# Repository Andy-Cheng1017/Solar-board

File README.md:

# Solar-board
太陽能板12V轉5V

含測試程式

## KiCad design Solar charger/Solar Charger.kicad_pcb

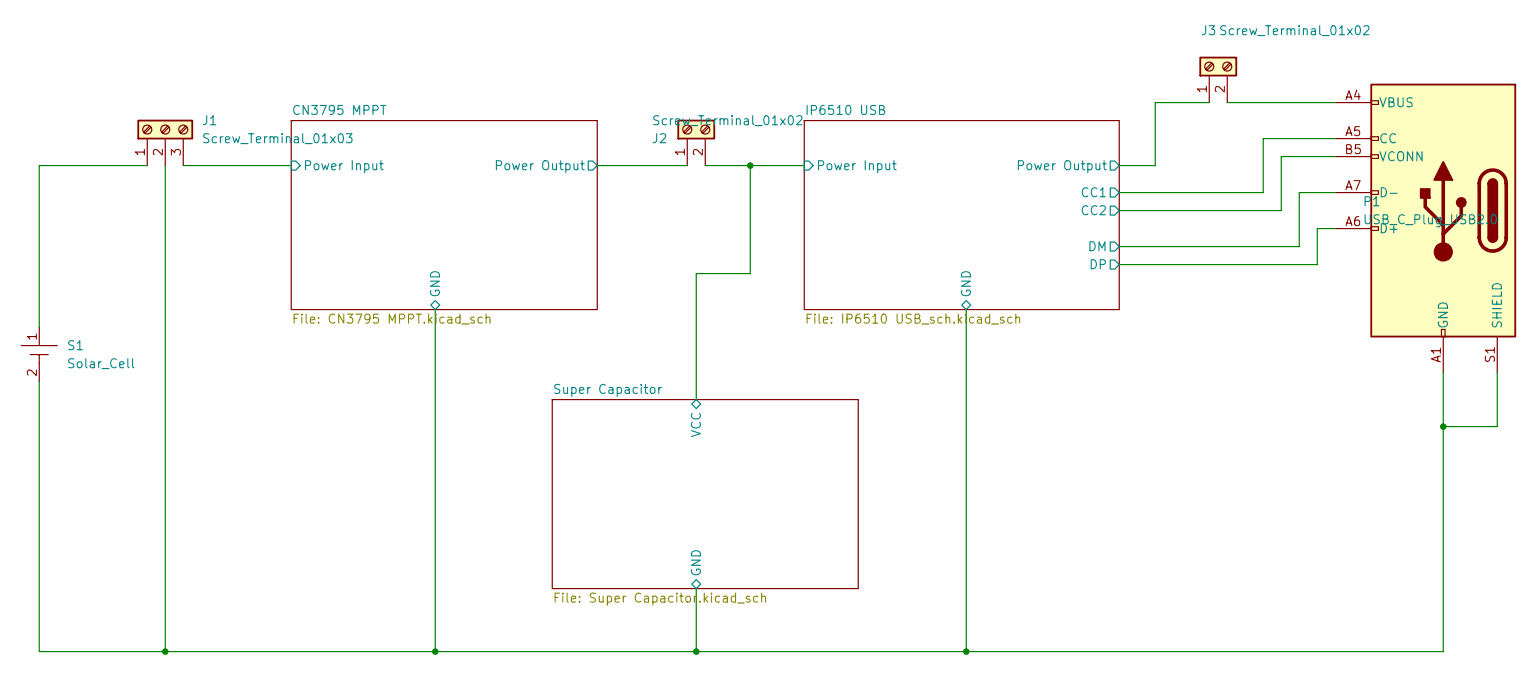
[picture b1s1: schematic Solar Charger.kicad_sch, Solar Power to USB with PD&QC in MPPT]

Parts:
J1: Screw_Terminal_01x03; TerminalBlock_bornier-3_P5.08mm
J2, J3: Screw_Terminal_01x02; TerminalBlock_bornier-2_P5.08mm
P1: USB_C_Plug_USB2.0; USB_C_Receptacle_HRO_TYPE-C-31-M-12
S1: Solar_Cell; TerminalBlock_bornier-2_P5.08mm

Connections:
/CN3795 MPPT/BAT: J2.1; also elsewhere on the board
/IP6510 USB/CC1: P1.A5 (CC); also elsewhere on the board
/IP6510 USB/CC2: P1.B5 (VCONN); also elsewhere on the board
/IP6510 USB/DM: P1.A7 (D-); also elsewhere on the board
/IP6510 USB/DP: P1.A6 (D+); also elsewhere on the board
/IP6510 USB/Power Input: J2.2; also elsewhere on the board
/IP6510 USB/Power Output: J3.1; also elsewhere on the board
GND: J1.2, P1.A1 (GND), P1.A12 (GND), P1.B1 (GND), P1.B12 (GND), P1.S1 (SHIELD), S1.2; also elsewhere on the board
unnamed: J1.1, S1.1
unnamed: J3.2, P1.A4 (VBUS), P1.A9 (VBUS), P1.B4 (VBUS), P1.B9 (VBUS)
VCC: J1.3; also elsewhere on the board

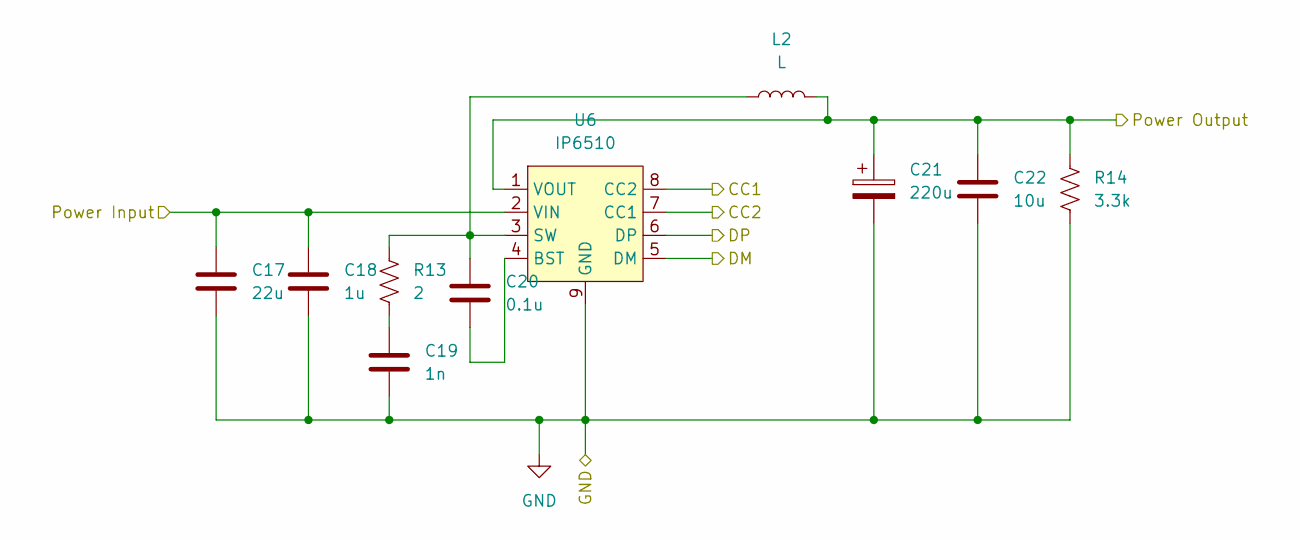
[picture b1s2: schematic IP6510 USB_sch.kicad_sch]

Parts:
C17: 22u; C_0805_2012Metric
C18: 1u; C_0805_2012Metric
C19: 1n; C_0805_2012Metric
C20: 0.1u; C_0805_2012Metric
C21: 220u; CP_Radial_D6.3mm_P2.50mm
C22: 10u; C_0805_2012Metric
L2: L; L_10.4x10.4_H4.8
R13: 2; R_0805_2012Metric
R14: 3.3k; R_0805_2012Metric
U6: IP6510; SOIC-8-1EP_3.9x4.9mm_P1.27mm_EP2.29x3mm_ThermalVias

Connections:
/IP6510 USB/CC1: U6.8 (CC2); also elsewhere on the board
/IP6510 USB/CC2: U6.7 (CC1); also elsewhere on the board
/IP6510 USB/DM: U6.5 (DM); also elsewhere on the board
/IP6510 USB/DP: U6.6 (DP); also elsewhere on the board
/IP6510 USB/Power Input: C17.1, C18.1, U6.2 (VIN); also elsewhere on the board
/IP6510 USB/Power Output: C21.1, C22.1, L2.2, R14.1, U6.1 (VOUT); also elsewhere on the board
GND: C17.2, C18.2, C19.2, C21.2, C22.2, R14.2, U6.9 (GND); also elsewhere on the board
unnamed: C19.1, R13.2
unnamed: C20.1, L2.1, R13.1, U6.3 (SW)
unnamed: C20.2, U6.4 (BST)

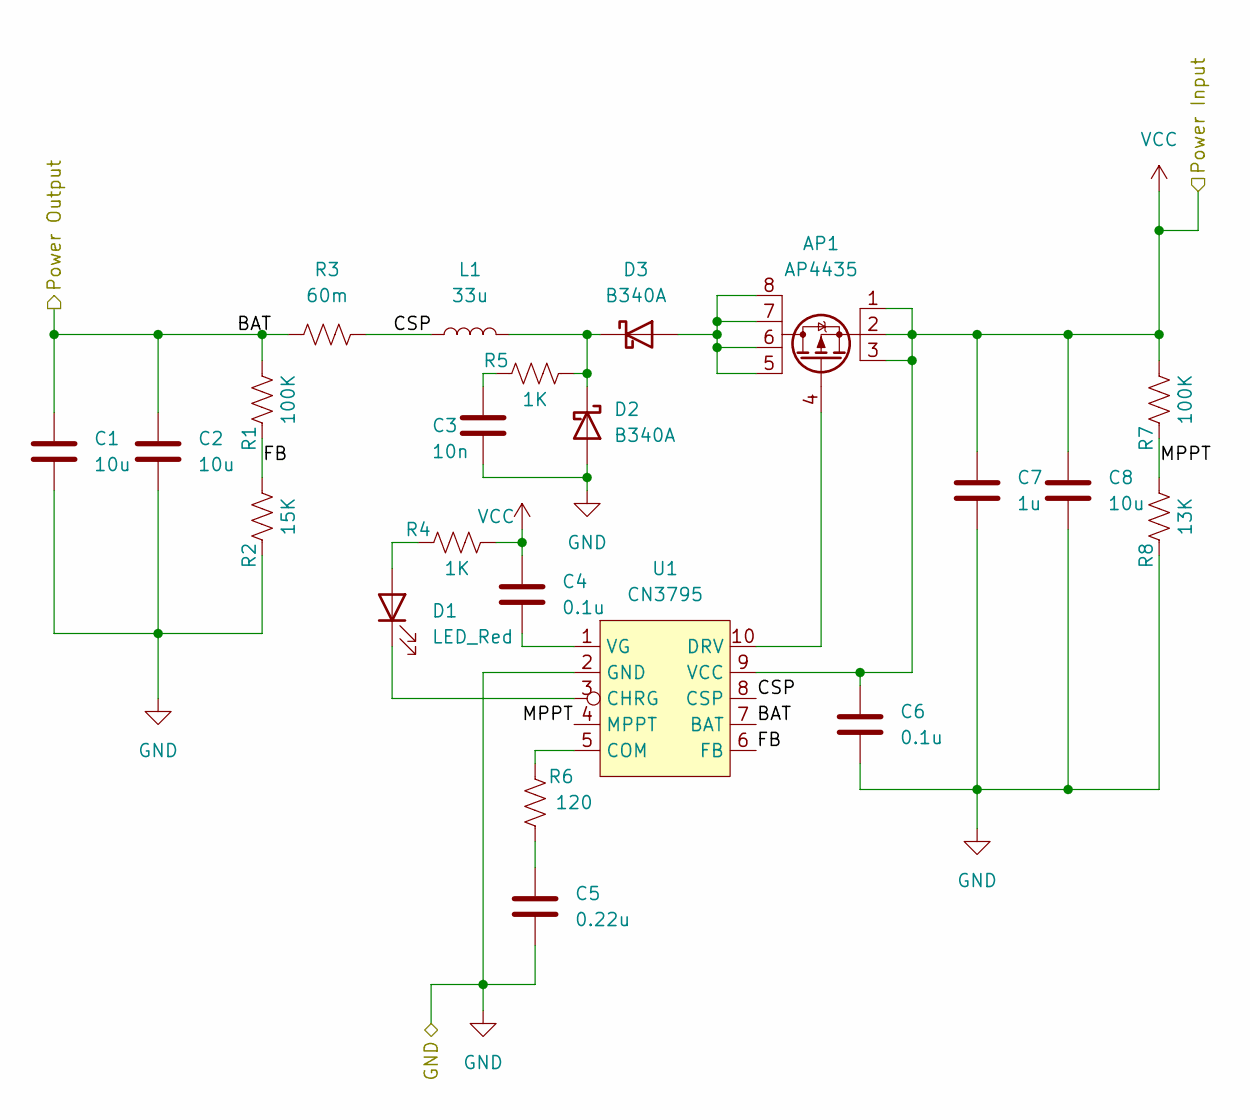
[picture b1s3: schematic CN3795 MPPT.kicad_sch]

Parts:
AP1: AP4435; PowerIntegrations_SO-8
C1, C2, C8: 10u; C_1206_3216Metric
C3: 10n; C_0805_2012Metric
C4, C6: 0.1u; C_0805_2012Metric
C5: 0.22u; C_0805_2012Metric
C7: 1u; C_0805_2012Metric
D1: LED_Red; LED_0805_2012Metric
D2, D3: B340A; D_SMA
L1: 33u; L_10.4x10.4_H4.8
R1, R7: 100K; R_0805_2012Metric
R2: 15K; R_0805_2012Metric
R3: 60m; R_2512_6332Metric
R4, R5: 1K; R_0805_2012Metric
R6: 120; R_0805_2012Metric
R8: 13K; R_0805_2012Metric
U1: CN3795; SSOP-10_3.9x4.9mm_P1.00mm

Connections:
/CN3795 MPPT/BAT: C1.1, C2.1, R1.2, R3.1, U1.7 (BAT); also elsewhere on the board
/CN3795 MPPT/CSP: L1.1, R3.2, U1.8 (CSP)
/CN3795 MPPT/FB: R1.1, R2.2, U1.6 (FB)
/CN3795 MPPT/MPPT: R7.1, R8.2, U1.4 (MPPT)
GND: C1.2, C2.2, C3.2, C5.1, C6.2, C7.2, C8.2, D2.2 (A), R2.1, R8.1, U1.2 (GND); also elsewhere on the board
unnamed: AP1.4 (G), U1.10 (DRV)
unnamed: AP1.5 (D), AP1.6 (D), AP1.7 (D), AP1.8 (D), D3.2 (A)
unnamed: C3.1, R5.1
unnamed: C4.2, U1.1 (VG)
unnamed: C5.2, R6.1
unnamed: D1.1 (K), U1.3 (CHRG)
unnamed: D1.2 (A), R4.1
unnamed: D2.1 (K), D3.1 (K), L1.2, R5.2
unnamed: R6.2, U1.5 (COM)
VCC: AP1.1 (S), AP1.2 (S), AP1.3 (f), C4.1, C6.1, C7.1, C8.1, R4.2, R7.2, U1.9 (VCC); also elsewhere on the board

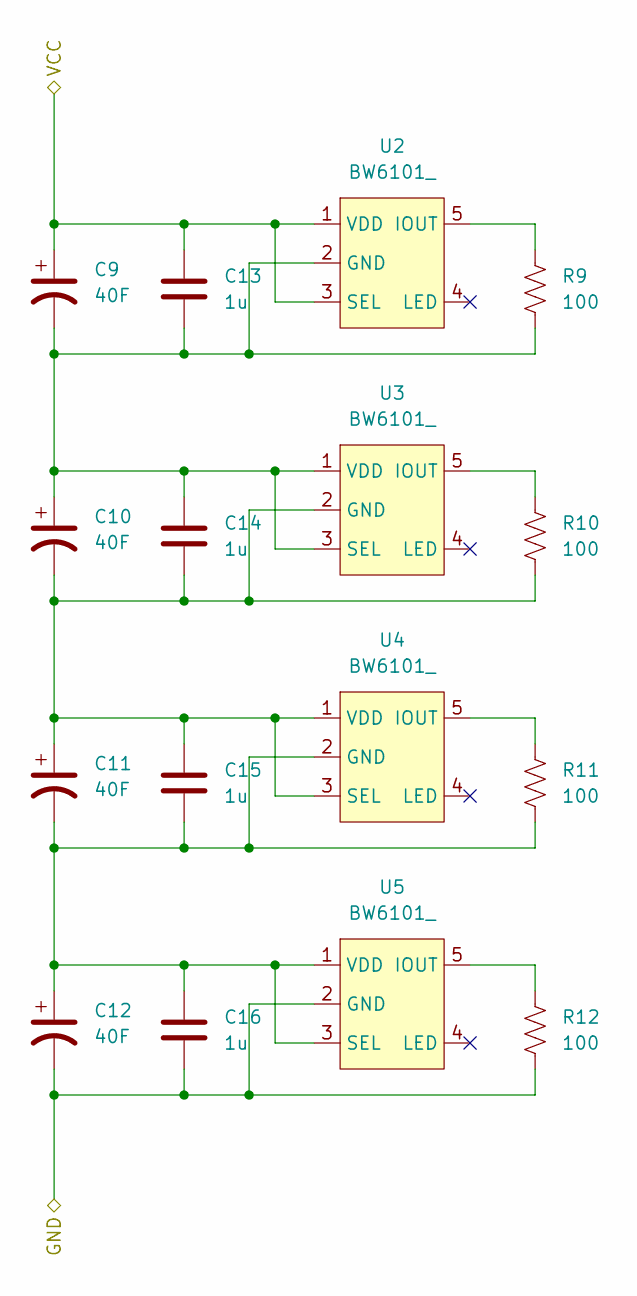
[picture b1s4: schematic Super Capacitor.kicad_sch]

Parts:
C9, C10, C11, C12: 40F; Super Capacitor
C13, C14, C15, C16: 1u; C_0805_2012Metric
R9, R10, R11, R12: 100; R_0805_2012Metric
U2, U3, U4, U5: BW6101_; SOT-23-5

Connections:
/IP6510 USB/Power Input: C9.1, C13.1, U2.1 (VDD), U2.3 (SEL); also elsewhere on the board
GND: C12.2, C16.2, R12.2, U5.2 (GND); also elsewhere on the board
unnamed: C9.2, C10.1, C13.2, C14.1, R9.2, U2.2 (GND), U3.1 (VDD), U3.3 (SEL)
unnamed: C10.2, C11.1, C14.2, C15.1, R10.2, U3.2 (GND), U4.1 (VDD), U4.3 (SEL)
unnamed: C11.2, C12.1, C15.2, C16.1, R11.2, U4.2 (GND), U5.1 (VDD), U5.3 (SEL)
unnamed: R9.1, U2.5 (IOUT)
unnamed: R10.1, U3.5 (IOUT)
unnamed: R11.1, U4.5 (IOUT)
unnamed: R12.1, U5.5 (IOUT)

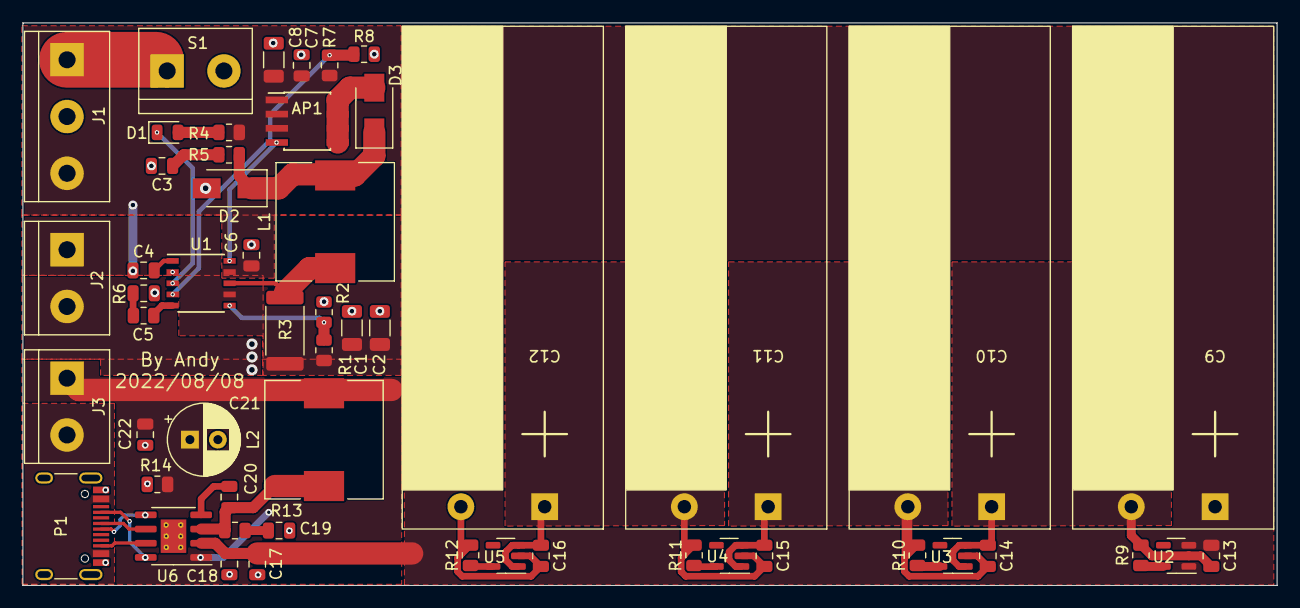
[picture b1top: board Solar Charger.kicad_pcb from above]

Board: 2 copper layers, 112.3 x 50.3 mm, 53 parts (0 on the bottom side), 33 nets.

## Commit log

2022-08-05 updata
2022-08-07 board compelet
2022-08-07 compelet
2022-09-15 增加新回測報告，單獨IP6050 BOM表
2022-09-17 增加電路圖PDF，新增修改一些元件
2022-09-22 加入新的測試報告
2022-09-22 加入太陽能板測試
2022-10-11 照片上傳
2023-08-08 強制更新
